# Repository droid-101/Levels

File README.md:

# Levels

Levels is an audio visualizer circuit board. When given audio signals as input, the board will display the magnitude of the sound on a row of LED lights.  The board is powered by a 9V battery and downsteps the voltage to 5V to power its components with an onboard voltage regulator. It supports audio input via an input AUX jack, and can output audio through either an output AUX jack, or a speaker.

## Circuit Components

### Amplification

The audio signal is inputted through the input AUX jack, and fed into the LM833N operational amplifier. The op amp is configured with set resistors and capacitors to amplify the incoming audio signals before they are sent to the output and the microcontroller. As to not cut off parts of audio signals, the op amp is raised to a virtual ground of 2.5V, rather than the IC's ground of 0V. A potentiometer is also part of this component of the circuit and can be used for tuning volume and clarity, as well as adjusting the sensitivity of the LED visualizer.

### Audio Processing

After amplification, the outputted audio signals are sent to the PIC16F690 microcontroller. A set of 6 sip pins on the board allow for a PicKit programmer to be connected to the board for reprogramming the PIC. Running on the microcontroller is an assembly program which determines the magnitude of the audio signal and turns on the appropriate number of LEDs. The internal ADCON register on the PIC manages the storing of sampled values of the audio signal. The read analog value is converted and stored in the ADRESL and ADRESH registers. After these registers are read, and a value representing the magnitude of the audio signal is obtained, the program decides which LEDs to turn on to represent the volume of the audio by writing bits to the PORTC register which the LEDs are connected to.

### Audio Output

The audio signals outputted by the amplifier are also routed to the output AUX jack and the speaker. A switch on the board controls which of the two components the audio signals are sent to. The speaker will play the audio directly from the board. The output AUX jack allows for headphones, or a small speaker to be connected to the board so that the audio can be played through an external device. Since the output volume can be different between the speaker and devices connected to the output jack, the potentiometer can be used to adjust the volume of the audio. Alternatively, the volume may be adjusted using the device which is playing the audio.

## Schematic

## Circuit Board

### Trace Mask

### Finished Circuit Board

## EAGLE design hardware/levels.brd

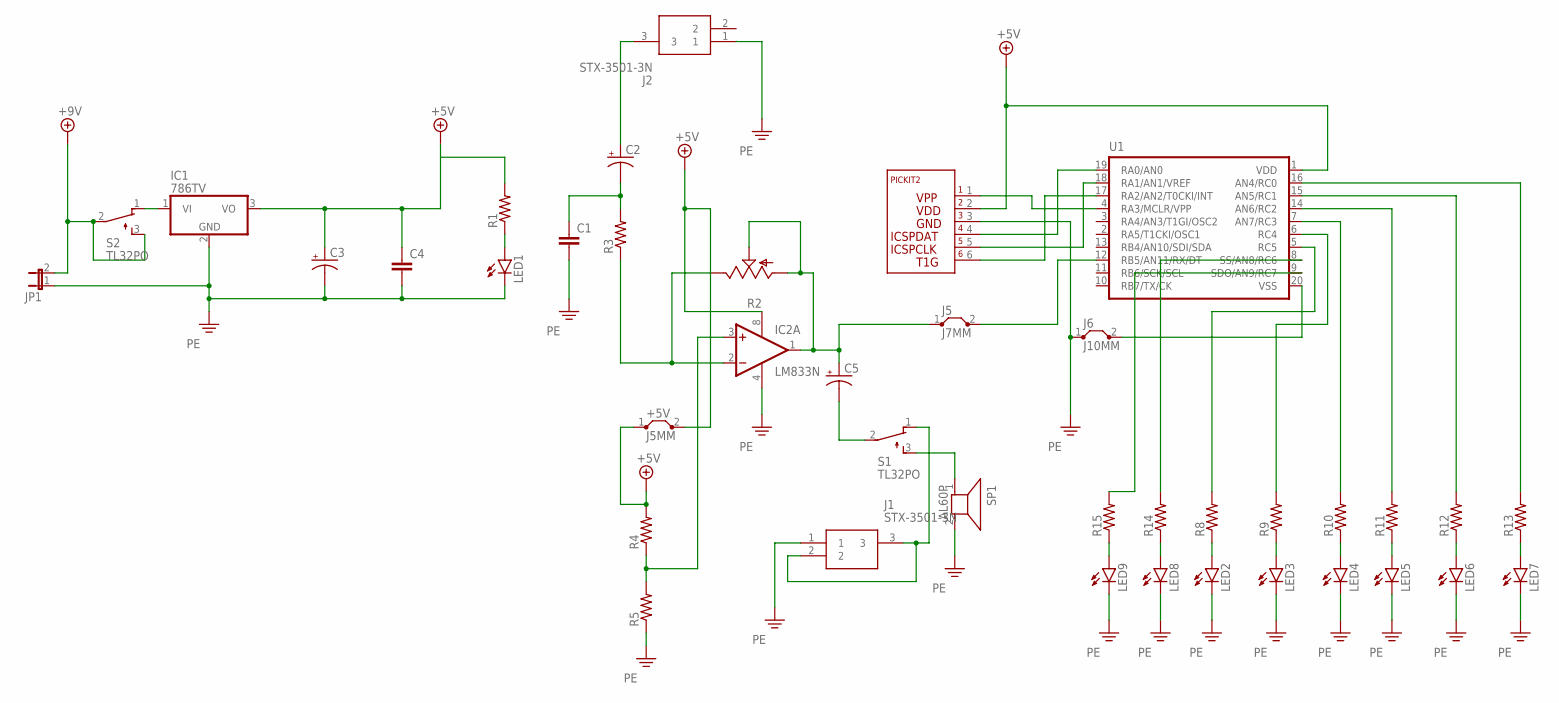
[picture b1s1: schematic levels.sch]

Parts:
+5V: J5MM; 05
C1, C4: C-EU025-024X044; C025-024X044
C2, C3, C5: CPOL-USE3.5-8; E3,5-8
IC1: 786TV; TO220V
IC2: LM833N; DIL08
J1, J2: STX-3501-3N; STX35013N
J5: J7MM; 07
J6: J10MM; 10
JP1: JP1E; JP1
LED1, LED2, LED3, LED4, LED5, LED6, LED7, LED8, LED9: LED5MM
R1, R3, R4, R5, R8, R9, R10, R11, R12, R13, R14, R15: R-US_0207/10; 0207/10
R2: TRIM_US-CA6V; CA6V
S1, S2: TL32PO; TL3XPO
SP1: AL60P
U1: PIC16F6XX; DIL20
U$1: PICKIT-ICSP; PICKITJUMPER

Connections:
+5V: +5V.1, +5V.2, C3.+, C4.1, IC1.3 (VO), IC2.8 (V+), R1.2, R4.2, U1.1 (VDD), U$1.2
+9V: JP1.2, S2.2, S2.3 (S)
unnamed: LED1.A, R1.1
unnamed: C1.1, C2.-, R3.2
unnamed: IC1.1 (VI), S2.1 (O)
unnamed: C5.-, S1.2
unnamed: S1.3 (S), SP1.1
unnamed: LED2.A, R8.1
unnamed: LED3.A, R9.1
unnamed: LED4.A, R10.1
unnamed: LED5.A, R11.1
unnamed: LED6.A, R12.1
unnamed: LED7.A, R13.1
unnamed: LED8.A, R14.1
unnamed: LED9.A, R15.1
unnamed: R13.2, U1.16 (AN4/RC0)
unnamed: R12.2, U1.15 (AN5/RC1)
unnamed: R11.2, U1.14 (AN6/RC2)
unnamed: R10.2, U1.7 (AN7/RC3)
unnamed: R9.2, U1.6 (RC4)
unnamed: R8.2, U1.5 (RC5)
unnamed: R14.2, U1.8 (SS/AN8/RC6)
unnamed: R15.2, U1.9 (SDO/AN9/RC7)
unnamed: U1.19 (RA0/AN0), U$1.4
unnamed: U1.18 (RA1/AN1/VREF), U$1.5
unnamed: U1.4 (RA3/MCLR/VPP), U$1.1
unnamed: U1.17 (RA2/AN2/T0CKI/INT), U$1.6
unnamed: C5.+, IC2.1 (OUT), J5.1, R2.A, R2.S
unnamed: IC2.2 (-IN), R2.E, R3.1
unnamed: IC2.3 (+IN), R4.1, R5.2
unnamed: C2.+, J2.3
unnamed: J1.2, J1.3, S1.1 (O)
unnamed: J6.2, U1.20 (VSS)
unnamed: J5.2, U1.12 (RB5/AN11/RX/DT)
PE: C1.2, C3.-, C4.2, IC1.2 (GND), IC2.4 (V-), J1.1, J2.1, J6.1, JP1.1, LED1.K (C), LED2.K (C), LED3.K (C), LED4.K (C), LED5.K (C), LED6.K (C), LED7.K (C), LED8.K (C), LED9.K (C), R5.1, SP1.2, U$1.3

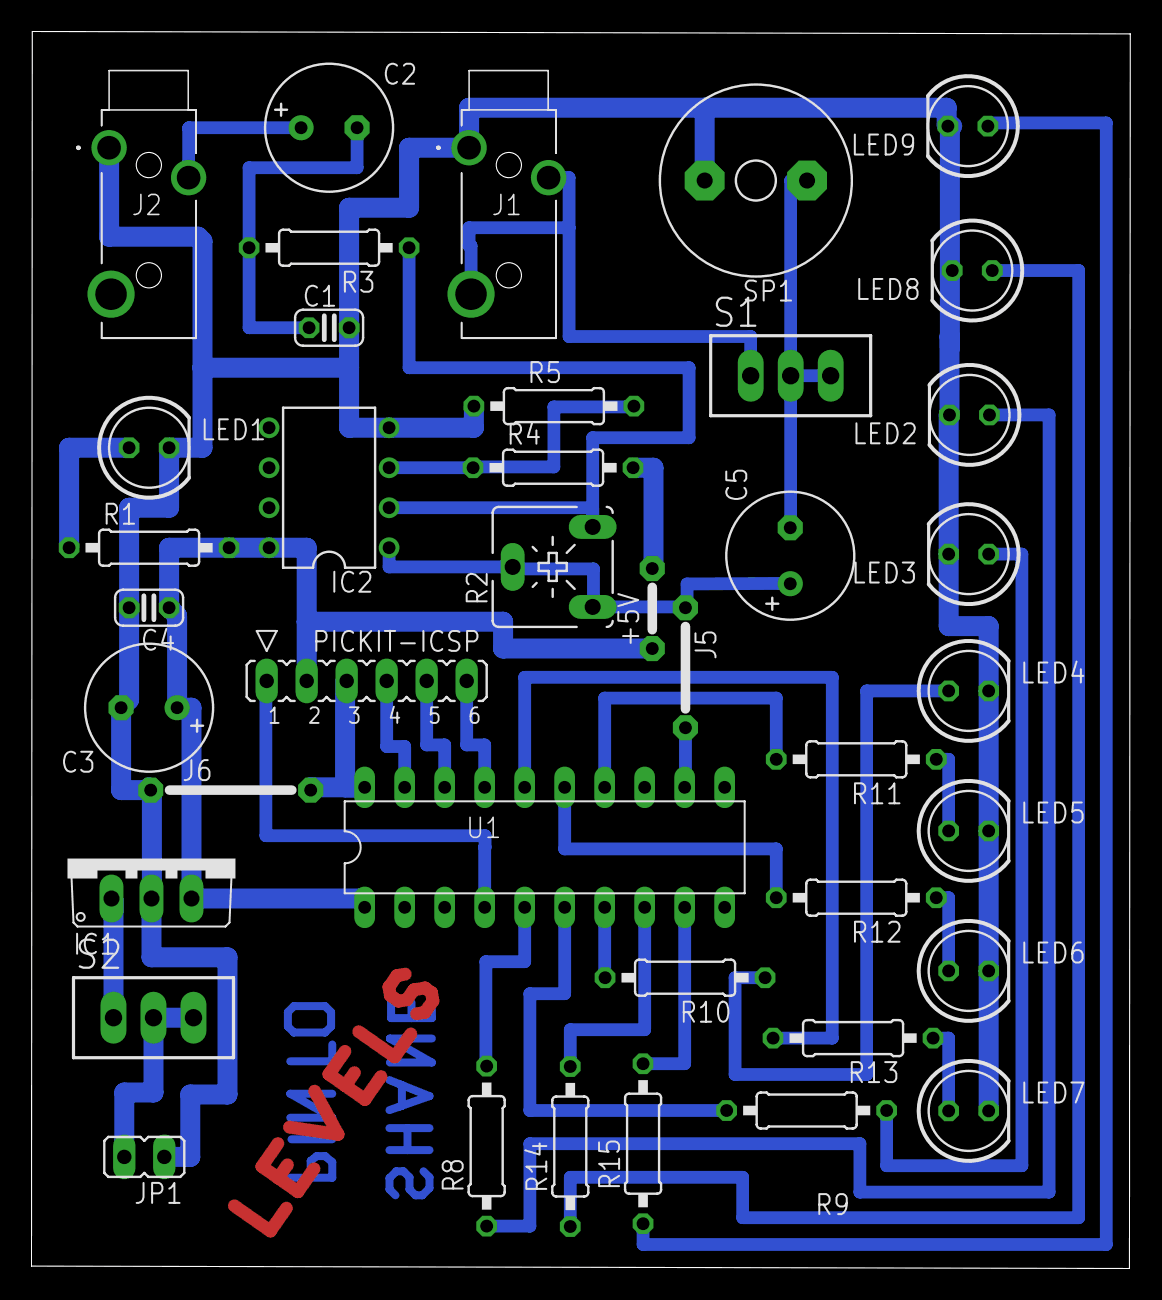
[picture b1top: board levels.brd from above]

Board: 2 copper layers, 69.8 x 78.6 mm, 40 parts (0 on the bottom side), 35 nets.

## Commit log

2023-01-03 Files
2023-01-09 Info Added
